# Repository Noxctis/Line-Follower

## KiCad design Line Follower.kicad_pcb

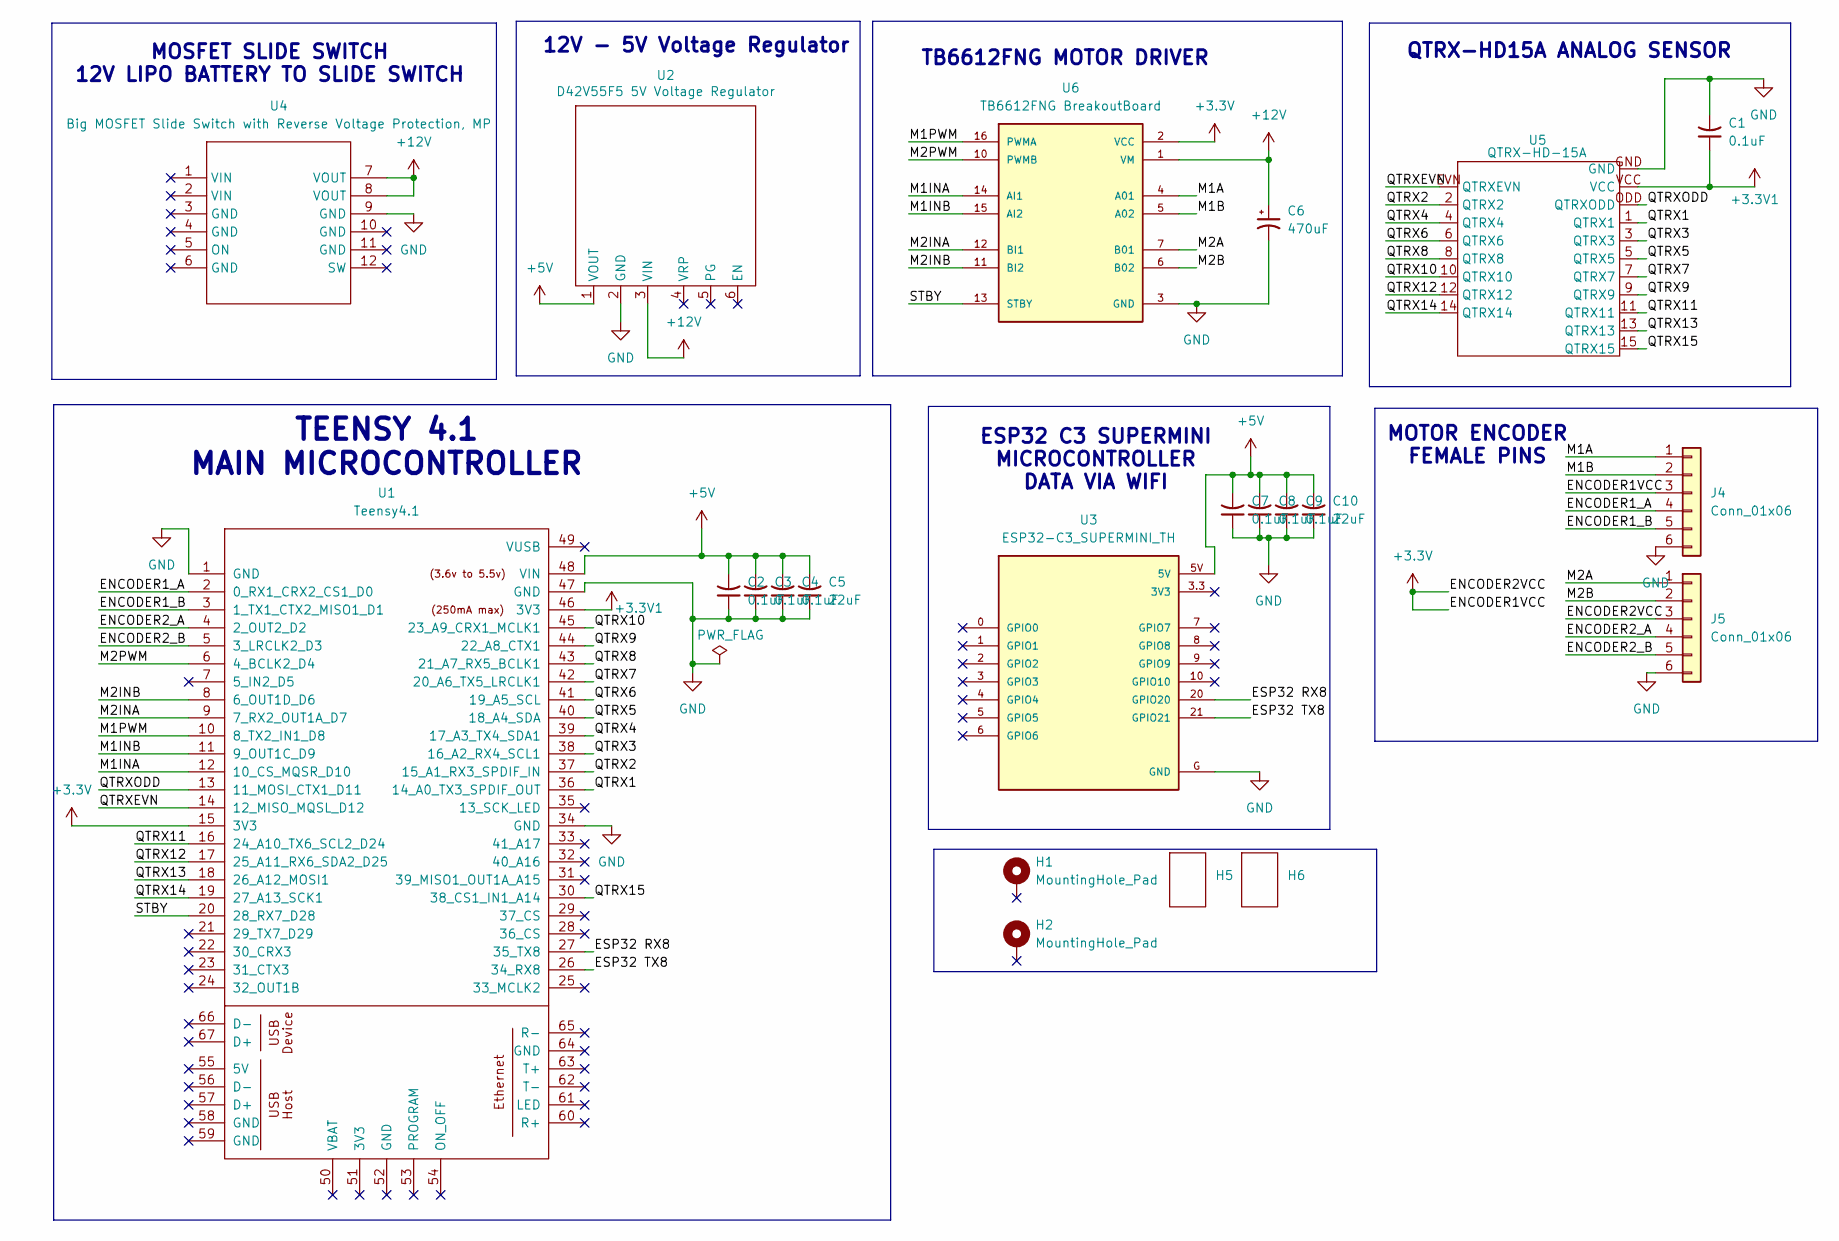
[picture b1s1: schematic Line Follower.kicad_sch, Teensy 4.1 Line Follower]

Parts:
C1, C2, C3, C4, C7, C8, C9: 0.1uF; C_0805_2012Metric_Pad1.18x1.45mm_HandSolder
C5, C10: 22uF; C_0805_2012Metric_Pad1.18x1.45mm_HandSolder
C6: 470uF; CP_Radial_D8.0mm_P3.50mm
H1, H2: MountingHole_Pad; MountingHole_2.2mm_M2_Pad_Via
H5, H6: Pololu Extended Motor Bracket
J4, J5: Conn_01x06; PinSocket_1x06_P2.54mm_Vertical
U1: Teensy4.1; Teensy41
U2: D42V55F5 5V Voltage Regulator; D42V55F5
U3: ESP32-C3_SUPERMINI_TH; MODULE_ESP32-C3_SUPERMINI_TH
U4: Big MOSFET Slide Switch with Reverse Voltage Prot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; Big MOSFET Slide Switch with Reverse Voltage Protection, MP
U5: QTRX-HD-15A
U6: TB6612FNG BreakoutBoard; MODULE_ROB-14450; PARTREV 11-13-17

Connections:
+3.3V: J4.3, J5.3, U1.15 (3V3), U6.2 (VCC)
+3.3V1: C1.1, U1.46 (3V3), U5.VCC
+5V: C2.2, C3.2, C4.2, C5.2, C7.2, C8.2, C9.2, C10.2, U1.48 (VIN), U2.1 (VOUT), U3.5V
+12V: C6.1, U2.3 (VIN), U4.7 (VOUT), U4.8 (VOUT), U6.1 (VM)
/ENCODER1_A: J4.4, U1.2 (0_RX1_CRX2_CS1_D0)
/ENCODER1_B: J4.5, U1.3 (1_TX1_CTX2_MISO1_D1)
/ENCODER2_A: J5.4, U1.4 (2_OUT2_D2)
/ENCODER2_B: J5.5, U1.5 (3_LRCLK2_D3)
/ESP32 RX8: U1.27 (35_TX8), U3.20 (GPIO20)
/ESP32 TX8: U1.26 (34_RX8), U3.21 (GPIO21)
/M1A: J4.1, U6.4 (A01)
/M1B: J4.2, U6.5 (A02)
/M1INA: U1.12 (10_CS_MQSR_D10), U6.14 (AI1)
/M1INB: U1.11 (9_OUT1C_D9), U6.15 (AI2)
/M1PWM: U1.10 (8_TX2_IN1_D8), U6.16 (PWMA)
/M2A: J5.1, U6.7 (B01)
/M2B: J5.2, U6.6 (B02)
/M2INA: U1.9 (7_RX2_OUT1A_D7), U6.12 (BI1)
/M2INB: U1.8 (6_OUT1D_D6), U6.11 (BI2)
/M2PWM: U1.6 (4_BCLK2_D4), U6.10 (PWMB)
/QTRX1: U1.36 (14_A0_TX3_SPDIF_OUT), U5.1 (QTRX1)
/QTRX2: U1.37 (15_A1_RX3_SPDIF_IN), U5.2 (QTRX2)
/QTRX3: U1.38 (16_A2_RX4_SCL1), U5.3 (QTRX3)
/QTRX4: U1.39 (17_A3_TX4_SDA1), U5.4 (QTRX4)
/QTRX5: U1.40 (18_A4_SDA), U5.5 (QTRX5)
/QTRX6: U1.41 (19_A5_SCL), U5.6 (QTRX6)
/QTRX7: U1.42 (20_A6_TX5_LRCLK1), U5.7 (QTRX7)
/QTRX8: U1.43 (21_A7_RX5_BCLK1), U5.8 (QTRX8)
/QTRX9: U1.44 (22_A8_CTX1), U5.9 (QTRX9)
/QTRX10: U1.45 (23_A9_CRX1_MCLK1), U5.10 (QTRX10)
/QTRX11: U1.16 (24_A10_TX6_SCL2_D24), U5.11 (QTRX11)
/QTRX12: U1.17 (25_A11_RX6_SDA2_D25), U5.12 (QTRX12)
/QTRX13: U1.18 (26_A12_MOSI1), U5.13 (QTRX13)
/QTRX14: U1.19 (27_A13_SCK1), U5.14 (QTRX14)
/QTRX15: U1.30 (38_CS1_IN1_A14), U5.15 (QTRX15)
/QTRXEVN: U1.14 (12_MISO_MQSL_D12), U5.EVN (QTRXEVN)
/QTRXODD: U1.13 (11_MOSI_CTX1_D11), U5.ODD (QTRXODD)
/STBY: U1.20 (28_RX7_D28), U6.13 (STBY)
GND: C1.2, C2.1, C3.1, C4.1, C5.1, C6.2, C7.1, C8.1, C9.1, C10.1, J4.6, J5.6, U1.1 (GND), U1.34 (GND), U1.47 (GND), U2.2 (GND), U3.G (GND), U4.9 (GND), U5.GND, U6.3 (GND), U6.8 (GND), U6.9 (GND)

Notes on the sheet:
TB6612FNG MOTOR DRIVER
ESP32 C3 SUPERMINI MICROCONTROLLER DATA VIA WIFI
MOSFET SLIDE SWITCH 12V LIPO BATTERY TO SLIDE SWITCH
QTRX-HD15A ANALOG SENSOR
TEENSY 4.1 MAIN MICROCONTROLLER
12V - 5V Voltage Regulator
MOTOR ENCODER FEMALE PINS

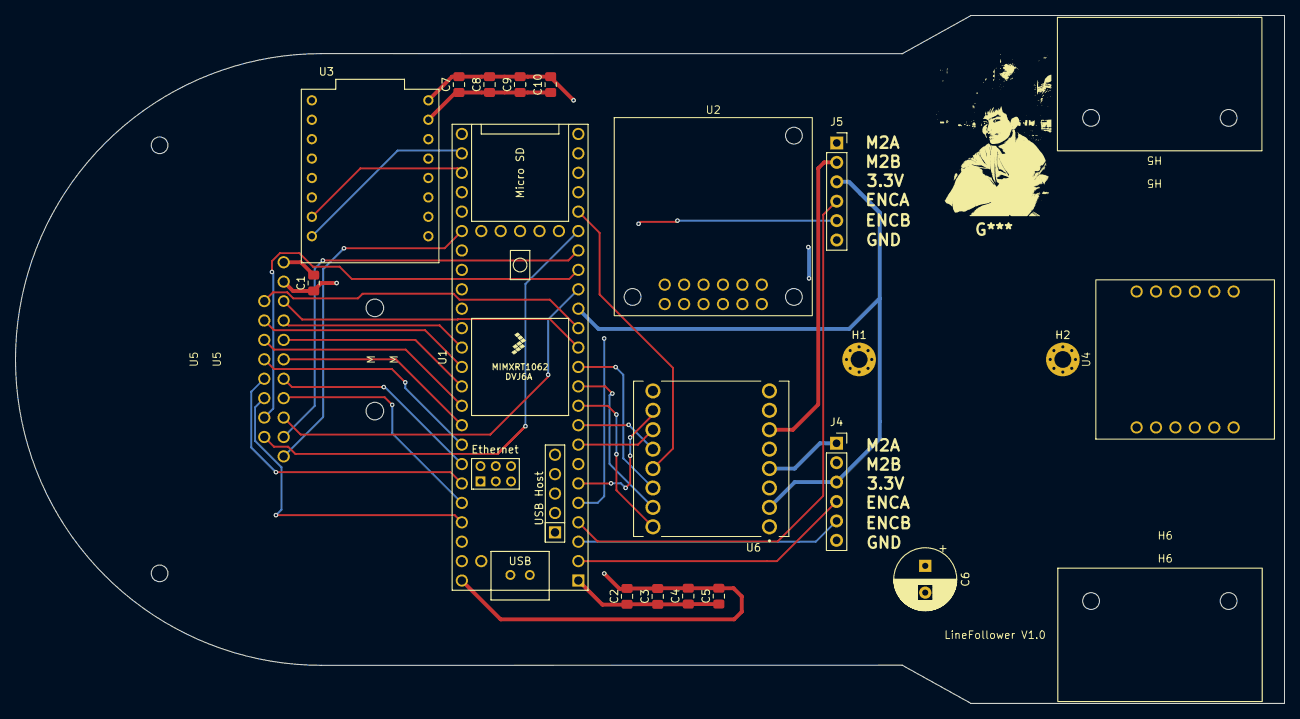
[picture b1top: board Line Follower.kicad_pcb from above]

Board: 4 copper layers, 166.0 x 90.0 mm, 23 parts (0 on the bottom side), 39 nets.

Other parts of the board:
M: Pololu Ball Castor

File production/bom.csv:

Designator,Footprint,Quantity,Value,LCSC Part #
"C1, C2, C3, C4, C7, C8, C9",0805,7,0.1uF,
"C10, C5",0805,2,22uF,
C6,CP_Radial_D8.0mm_P3.50mm,1,470uF,
"H5, H6",Pololu Extended Motor Bracket,2,~,
"J4, J5",PinSocket_1x06_P2.54mm_Vertical,2,Conn_01x06,
M,Pololu Ball Castor,1,Pololu Ball Castor,
U1,Teensy41,1,Teensy4.1,
U2,D42V55F5,1,D42V55F5 5V Voltage Regulator,
U3,MODULE_ESP32-C3_SUPERMINI_TH,1,ESP32-C3_SUPERMINI_TH,
U4,"Big MOSFET Slide Switch with Reverse Voltage Protection, MP",1,"Big MOSFET Slide Switch with Reverse Voltage Protection, MP",
U5,QTRX-HD-15A,1,QTRX-HD-15A,
U6,MODULE_ROB-14450,1,TB6612FNG BreakoutBoard,

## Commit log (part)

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2025-07-21 Refactor code structure for improved readability and maintainability
2025-09-01 Add PCB routing rules and lock files for Line Follower project
    - Created a new freerouting.rules file with detailed autorouting settings, layer rules, via definitions, and clearance classes for the PCB design.
    - Added lock files for both the PCB and schematic to track user session information.
2025-09-01 Rectangular Form before deletion
2025-09-01 Update active layer in project settings from 2 to 6 for improved design visibility
2025-09-01 Empty commit with no code changes made.
2026-02-25 Version1.0 QTRX-HD15A
